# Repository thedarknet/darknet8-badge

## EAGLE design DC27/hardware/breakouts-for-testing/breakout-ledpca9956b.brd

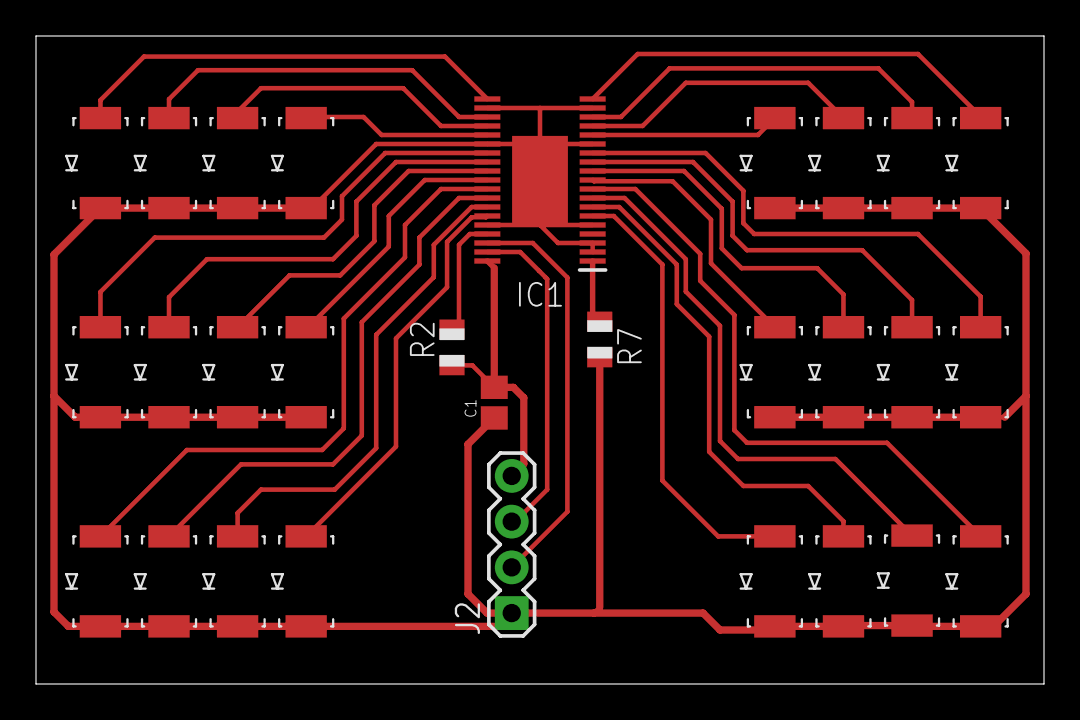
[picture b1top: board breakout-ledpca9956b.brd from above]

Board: 2 copper layers, 56.0 x 36.0 mm, 30 parts (0 on the bottom side), 30 nets.

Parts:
C1: 0.1 uF; C0805
IC1: PCA9956BTWY; SOP50P640X110-39N
J2: 1X04
LED1, LED2, LED3, LED4, LED5, LED6, LED7, LED8, LED9, LED10, LED11, LED12, LED13, LED14, LED15, LED16, LED17, LED18, LED19, LED20, LED21, LED22, LED23, LED24: GULLWING_LED
R2: 10 K; R0805
R7: 2 K; R0805
U$2: CMD_C0DE_LOGO

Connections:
GND: C1.1, IC1.2, IC1.3, IC1.5, IC1.14, IC1.18, IC1.21, IC1.25, IC1.34, IC1.39, J2.1, LED1.C, LED2.C, LED3.C, LED4.C, LED5.C, LED6.C, LED7.C, LED8.C, LED9.C, LED10.C, LED11.C, LED12.C, LED13.C, LED14.C, LED15.C, LED16.C, LED17.C, LED18.C, LED19.C, LED20.C, LED21.C, LED22.C, LED23.C, LED24.C, R7.2
unnamed: IC1.6, LED1.A
unnamed: IC1.7, LED2.A
unnamed: IC1.8, LED3.A
unnamed: IC1.9, LED4.A
unnamed: IC1.10, LED5.A
unnamed: IC1.11, LED6.A
unnamed: IC1.12, LED7.A
unnamed: IC1.13, LED8.A
unnamed: IC1.15, LED9.A
unnamed: IC1.16, LED10.A
unnamed: IC1.17, LED11.A
unnamed: IC1.19, LED12.A
unnamed: IC1.20, LED13.A
unnamed: IC1.22, LED14.A
unnamed: IC1.23, LED15.A
unnamed: IC1.24, LED16.A
unnamed: IC1.26, LED17.A
unnamed: IC1.27, LED18.A
unnamed: IC1.28, LED19.A
unnamed: IC1.29, LED20.A
unnamed: IC1.30, LED21.A
unnamed: IC1.31, LED22.A
unnamed: IC1.32, LED23.A
unnamed: IC1.33, LED24.A
unnamed: IC1.1, R7.1
unnamed: IC1.35, R2.2
SCL: IC1.36, J2.2
SDA: IC1.37, J2.3
VCC: C1.2, IC1.38, J2.4, R2.1

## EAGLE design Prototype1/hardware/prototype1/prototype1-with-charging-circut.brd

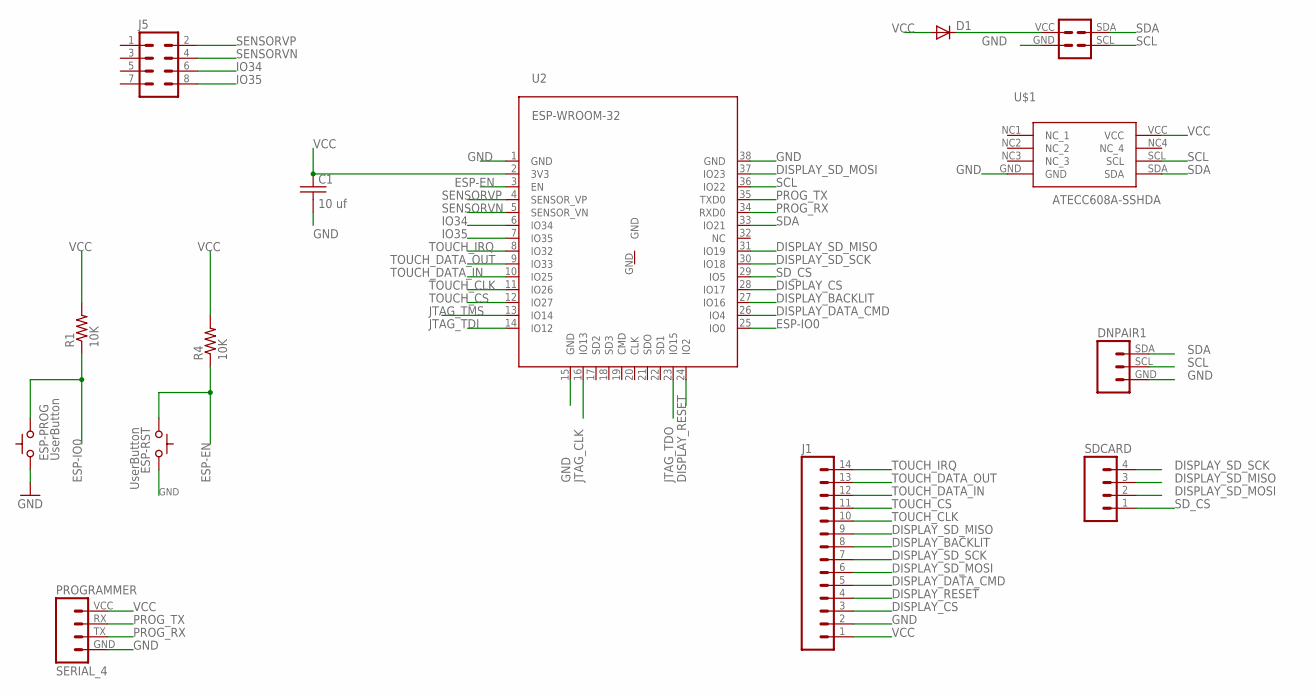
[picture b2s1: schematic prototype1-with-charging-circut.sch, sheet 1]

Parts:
C1: 10 uf; C0805
D1: DIODESMA; SMA-DIODE
DNPAIR1: DARKNET_8_PAIR_CONNECTORPTH; 1X03
ESP-PROG: UserButton; TACTILE-2PIN-NARROW
ESP-RST: UserButton; TACTILE-2PIN-NARROW
J1: M14; 1X14
J5: M04X2; 2X4
PROGRAMMER: SERIAL_4; SERIAL_HEADER_4
R1, R4: 10K; 0805
SDCARD: M04PTH; 1X04
SHITTY_ADDON: SAO1; DC26SHITTY_ADDON_CONNECTOR
U2: ESP-WROOM-32
U$1: ATECC608A-SSHDA; 8-SOIC

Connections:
DISPLAY_BACKLIT: J1.8, U2.27 (IO16)
DISPLAY_CS: J1.3, U2.28 (IO17)
DISPLAY_DATA_CMD: J1.5, U2.26 (IO4)
DISPLAY_RESET: J1.4, U2.24 (IO2)
DISPLAY_SD_MISO: J1.9, SDCARD.3, U2.31 (IO19)
DISPLAY_SD_MOSI: J1.6, SDCARD.2, U2.37 (IO23)
DISPLAY_SD_SCK: J1.7, SDCARD.4, U2.30 (IO18)
ESP-EN: ESP-RST.P$2 (C), R4.1, U2.3 (EN)
ESP-IO0: ESP-PROG.P$1 (A), R1.1, U2.25 (IO0)
GND: C1.2, DNPAIR1.GND, ESP-PROG.P$2 (C), ESP-RST.P$1 (A), J1.2, PROGRAMMER.GND, SHITTY_ADDON.GND, U2.1 (GND), U2.15 (GND), U2.38 (GND), U$1.GND; also elsewhere on the board
IO34: J5.6, U2.6 (IO34)
IO35: J5.8, U2.7 (IO35)
JTAG_CLK: U2.16 (IO13); also elsewhere on the board
JTAG_TDI: U2.14 (IO12); also elsewhere on the board
JTAG_TDO: U2.23 (IO15); also elsewhere on the board
JTAG_TMS: U2.13 (IO14); also elsewhere on the board
unnamed: D1.C, SHITTY_ADDON.VCC
PROG_RX: PROGRAMMER.TX, U2.34 (RXD0); also elsewhere on the board
PROG_TX: PROGRAMMER.RX, U2.35 (TXD0); also elsewhere on the board
SCL: DNPAIR1.SCL, SHITTY_ADDON.SCL, U2.36 (IO22), U$1.SCL
SDA: DNPAIR1.SDA, SHITTY_ADDON.SDA, U2.33 (IO21), U$1.SDA
SD_CS: SDCARD.1, U2.29 (IO5)
SENSORVN: J5.4, U2.5 (SENSOR_VN)
SENSORVP: J5.2, U2.4 (SENSOR_VP)
TOUCH_CLK: J1.10, U2.11 (IO26)
TOUCH_CS: J1.11, U2.12 (IO27)
TOUCH_DATA_IN: J1.12, U2.10 (IO25)
TOUCH_DATA_OUT: J1.13, U2.9 (IO33)
TOUCH_IRQ: J1.14, U2.8 (IO32)
VCC: C1.1, D1.A, J1.1, PROGRAMMER.VCC, R1.2, R4.2, U2.2 (3V3), U$1.VCC; also elsewhere on the board

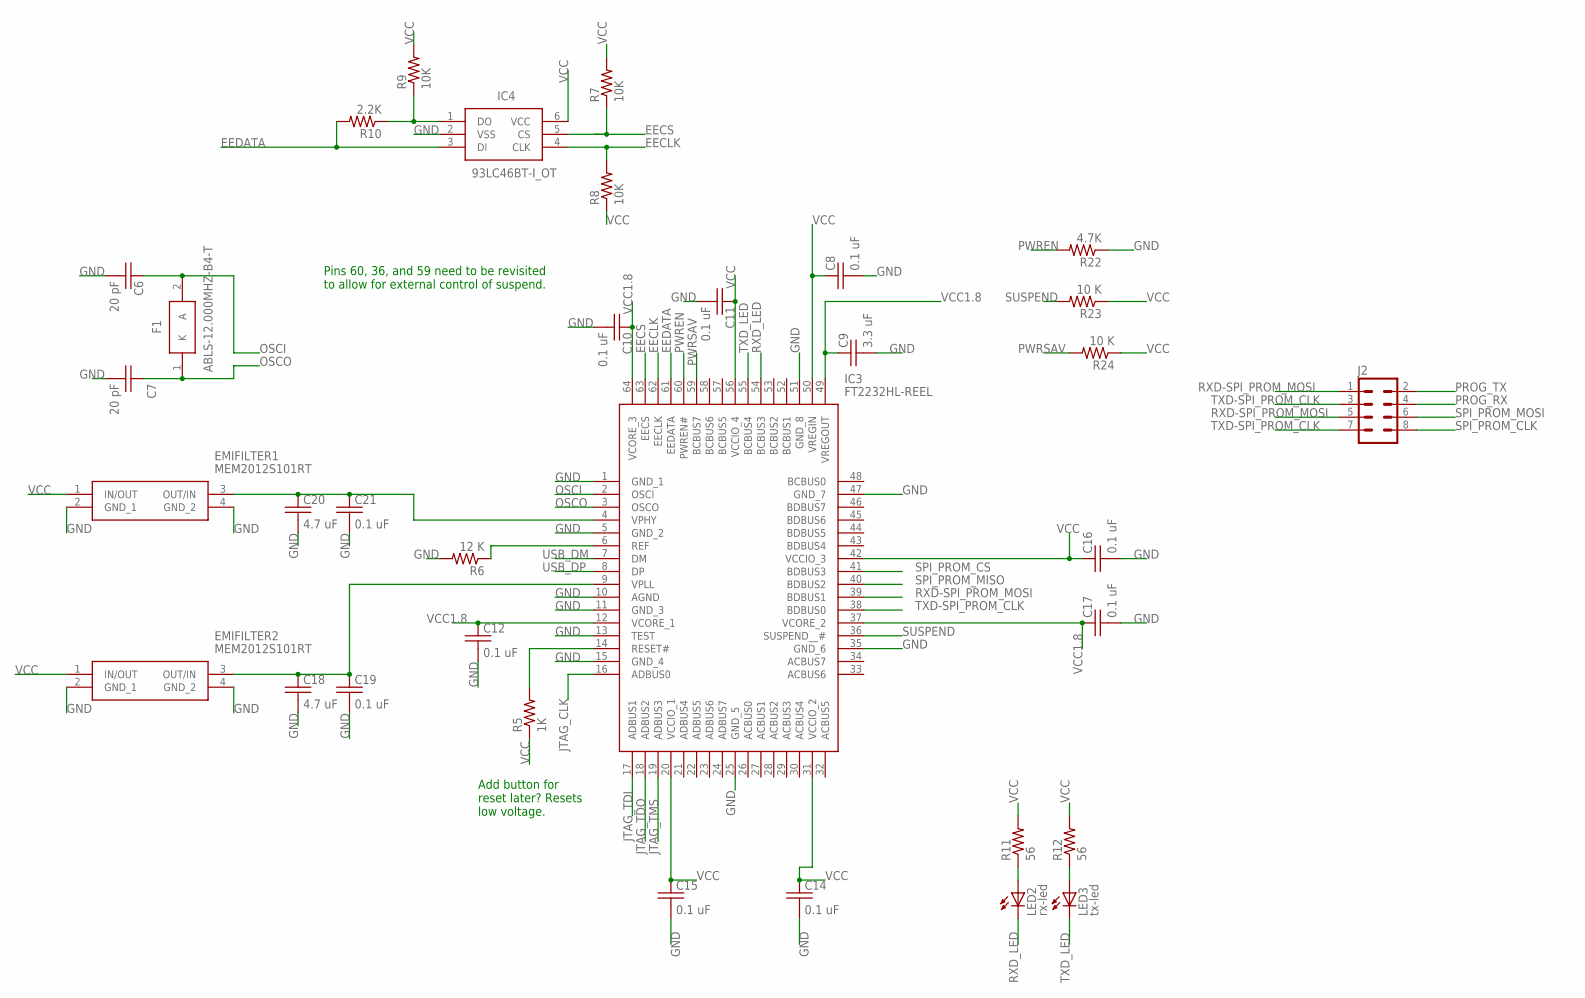
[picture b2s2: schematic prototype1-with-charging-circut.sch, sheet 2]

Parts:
C6, C7: 20 pF; C0805
C8, C10, C11, C12, C14, C15, C16, C17, C19, C21: 0.1 uF; C0805
C9: 3.3 uF; C0805
C18, C20: 4.7 uF; C0805
EMIFILTER1, EMIFILTER2: MEM2012S101RT
F1: ABLS-12.000MHZ-B4-T; HC/49US-(AT49)_1
IC3: FT2232HL-REEL; QFP50P1200X1200X160-64N
IC4: 93LC46BT-I_OT; SOT95P270X145-6N
J2: M04X2; 2X4
LED2: rx-led; LED3MM
LED3: tx-led; LED3MM
R5: 1K; 0805
R6: 12 K; 0805
R7, R8, R9: 10K; 0805
R10: 2.2K; 0805
R11, R12: 56; 0805
R22: 4.7K; 0805
R23, R24: 10 K; 0805

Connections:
EECLK: IC3.62 (EECLK), IC4.4 (CLK), R8.2
EECS: IC3.63 (EECS), IC4.5 (CS), R7.1
EEDATA: IC3.61 (EEDATA), IC4.3 (DI), R10.2
GND: C6.2, C7.2, C8.2, C9.2, C10.2, C11.2, C12.2, C14.2, C15.2, C16.2, C17.2, C18.2, C19.2, C20.2, C21.2, EMIFILTER1.2 (GND_1), EMIFILTER1.4 (GND_2), EMIFILTER2.2 (GND_1), EMIFILTER2.4 (GND_2), IC3.1 (GND_1), IC3.5 (GND_2), IC3.10 (AGND), IC3.11 (GND_3), IC3.13 (TEST), IC3.15 (GND_4), IC3.25 (GND_5), IC3.35 (GND_6), IC3.47 (GND_7), IC3.51 (GND_8), IC4.2 (VSS), R6.2, R22.1; also elsewhere on the board
JTAG_CLK: IC3.16 (ADBUS0); also elsewhere on the board
JTAG_TDI: IC3.17 (ADBUS1); also elsewhere on the board
JTAG_TDO: IC3.18 (ADBUS2); also elsewhere on the board
JTAG_TMS: IC3.19 (ADBUS3); also elsewhere on the board
unnamed: IC3.14 (RESET#), R5.2
unnamed: IC3.6 (REF), R6.1
unnamed: IC4.1 (DO), R9.1, R10.1
unnamed: LED2.A, R11.1
unnamed: LED3.A, R12.1
unnamed: C18.1, C19.1, EMIFILTER2.3 (OUT/IN), IC3.9 (VPLL)
unnamed: C20.1, C21.1, EMIFILTER1.3 (OUT/IN), IC3.4 (VPHY)
OSCI: C6.1, F1.2 (A), IC3.2 (OSCI)
OSCO: C7.1, F1.1 (K), IC3.3 (OSCO)
PROG_RX: J2.4; also elsewhere on the board
PROG_TX: J2.2; also elsewhere on the board
PWREN: IC3.60 (PWREN#), R22.2
PWRSAV: IC3.59 (BCBUS7), R24.2
RXD-SPI_PROM_MOSI: IC3.39 (BDBUS1), J2.1, J2.5
RXD_LED: IC3.54 (BCBUS3), LED2.K (C)
SPI_PROM_CLK: J2.8; also elsewhere on the board
SPI_PROM_CS: IC3.41 (BDBUS3); also elsewhere on the board
SPI_PROM_MISO: IC3.40 (BDBUS2); also elsewhere on the board
SPI_PROM_MOSI: J2.6; also elsewhere on the board
SUSPEND: IC3.36 (SUSPEND__#), R23.2
TXD-SPI_PROM_CLK: IC3.38 (BDBUS0), J2.3, J2.7
TXD_LED: IC3.55 (BCBUS4), LED3.K (C)
USB_DM: IC3.7 (DM); also elsewhere on the board
USB_DP: IC3.8 (DP); also elsewhere on the board
VCC: C8.1, C11.1, C14.1, C15.1, C16.1, EMIFILTER1.1 (IN/OUT), EMIFILTER2.1 (IN/OUT), IC3.20 (VCCIO_1), IC3.31 (VCCIO_2), IC3.42 (VCCIO_3), IC3.50 (VREGIN), IC3.56 (VCCIO_4), IC4.6 (VCC), R5.1, R7.2, R8.1, R9.2, R11.2, R12.2, R23.1, R24.1; also elsewhere on the board
VCC1.8: C9.1, C10.1, C12.1, C17.1, IC3.12 (VCORE_1), IC3.37 (VCORE_2), IC3.49 (VREGOUT), IC3.64 (VCORE_3)

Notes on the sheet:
Add button for reset later? Resets low voltage.
Pins 60, 36, and 59 need to be revisited to allow for external control of suspend.

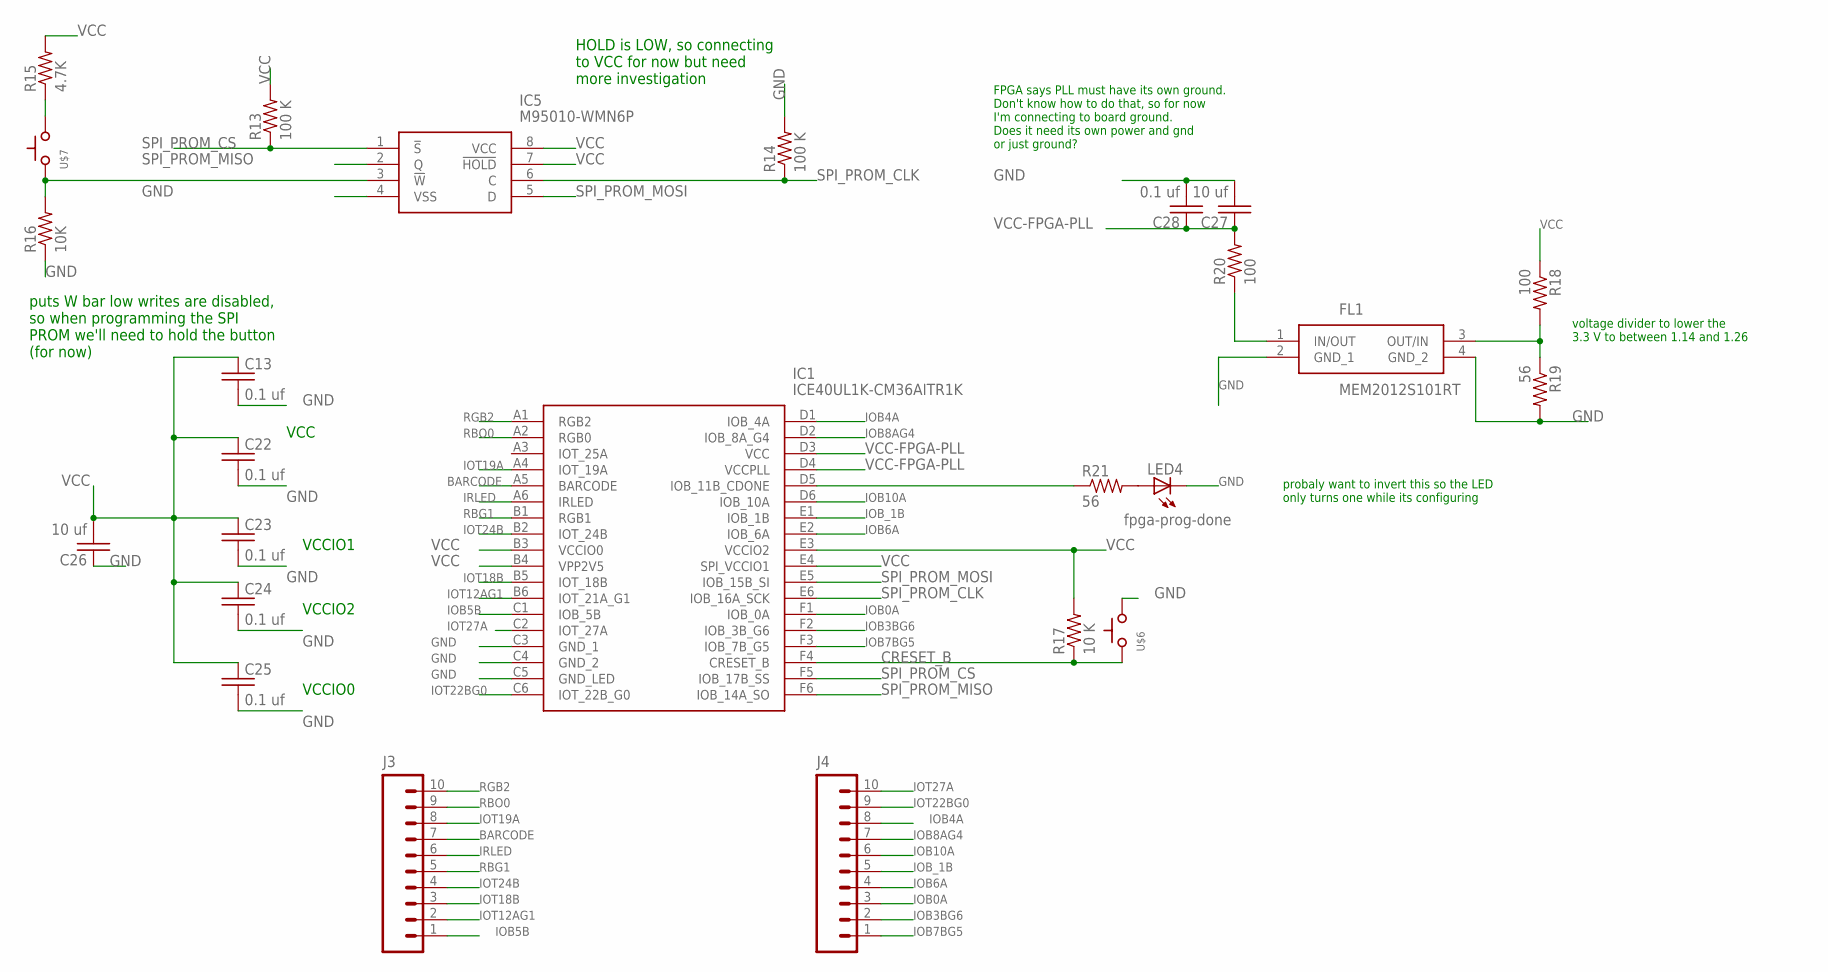
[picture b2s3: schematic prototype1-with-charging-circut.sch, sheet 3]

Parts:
C13, C22, C23, C24, C25, C28: 0.1 uf; C0805
C26, C27: 10 uf; C0805
FL1: MEM2012S101RT
IC1: ICE40UL1K-CM36AITR1K; BGA36C40P6X6_250X250X91
IC5: M95010-WMN6P; SOIC127P600X175-8N
J3, J4: M10SILK_FEMALE_PTH; 1X10
LED4: fpga-prog-done; LED3MM
R13, R14: 100 K; 0805
R15: 4.7K; 0805
R16: 10K; 0805
R17: 10 K; 0805
R18, R20: 100; 0805
R19, R21: 56; 0805
U$6, U$7: SWITCH_TACTILETACTILE-2PIN; TACTILE-2PIN

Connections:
BARCODE: IC1.A5 (BARCODE), J3.7
CRESET_B: IC1.F4 (CRESET_B), R17.1, U$6.P$2 (C)
GND: C13.2, C22.2, C23.2, C24.2, C25.2, C26.1, C27.2, C28.2, FL1.2 (GND_1), FL1.4 (GND_2), IC1.C3 (GND_1), IC1.C4 (GND_2), IC1.C5 (GND_LED), IC5.4 (VSS), LED4.K (C), R14.2, R16.1, R19.2, U$6.P$1 (A); also elsewhere on the board
IOB0A: IC1.F1 (IOB_0A), J4.3
IOB3BG6: IC1.F2 (IOB_3B_G6), J4.2
IOB4A: IC1.D1 (IOB_4A), J4.8
IOB5B: IC1.C1 (IOB_5B), J3.1
IOB6A: IC1.E2 (IOB_6A), J4.4
IOB7BG5: IC1.F3 (IOB_7B_G5), J4.1
IOB8AG4: IC1.D2 (IOB_8A_G4), J4.7
IOB10A: IC1.D6 (IOB_10A), J4.6
IOB_1B: IC1.E1 (IOB_1B), J4.5
IOT12AG1: IC1.B6 (IOT_21A_G1), J3.2
IOT18B: IC1.B5 (IOT_18B), J3.3
IOT19A: IC1.A4 (IOT_19A), J3.8
IOT22BG0: IC1.C6 (IOT_22B_G0), J4.9
IOT24B: IC1.B2 (IOT_24B), J3.4
IOT27A: IC1.C2 (IOT_27A), J4.10
IRLED: IC1.A6 (IRLED), J3.6
unnamed: IC5.3 (!W), R16.2, U$7.P$2 (C)
unnamed: R15.1, U$7.P$1 (A)
unnamed: LED4.A, R21.2
unnamed: FL1.3 (OUT/IN), R18.2, R19.1
unnamed: FL1.1 (IN/OUT), R20.1
unnamed: IC1.D5 (IOB_11B_CDONE), R21.1
RBG1: IC1.B1 (RGB1), J3.5
RBO0: IC1.A2 (RGB0), J3.9
RGB2: IC1.A1 (RGB2), J3.10
SPI_PROM_CLK: IC1.E6 (IOB_16A_SCK), IC5.6 (C), R14.1; also elsewhere on the board
SPI_PROM_CS: IC1.F5 (IOB_17B_SS), IC5.1 (!S), R13.1; also elsewhere on the board
SPI_PROM_MISO: IC1.F6 (IOB_14A_SO), IC5.2 (Q); also elsewhere on the board
SPI_PROM_MOSI: IC1.E5 (IOB_15B_SI), IC5.5 (D); also elsewhere on the board
VCC: C13.1, C22.1, C23.1, C24.1, C25.1, C26.2, IC1.B3 (VCCIO0), IC1.B4 (VPP2V5), IC1.E3 (VCCIO2), IC1.E4 (SPI_VCCIO1), IC5.7 (!HOLD), IC5.8 (VCC), R13.2, R15.2, R17.2, R18.1; also elsewhere on the board
VCC-FPGA-PLL: C27.1, C28.1, IC1.D3 (VCC), IC1.D4 (VCCPLL), R20.2

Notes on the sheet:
HOLD is LOW, so connecting to VCC for now but need more investigation
puts W bar low writes are disabled, so when programming the SPI PROM we'll need to hold the button (for now)
voltage divider to lower the 3.3 V to between 1.14 and 1.26
VCC
VCCIO1
VCCIO2
VCCIO0
FPGA says PLL must have its own ground. Don't know how to do that, so for now I'm connecting to board ground. Does it need its own power and gnd or just ground?
probaly want to invert this so the LED only turns one while its configuring

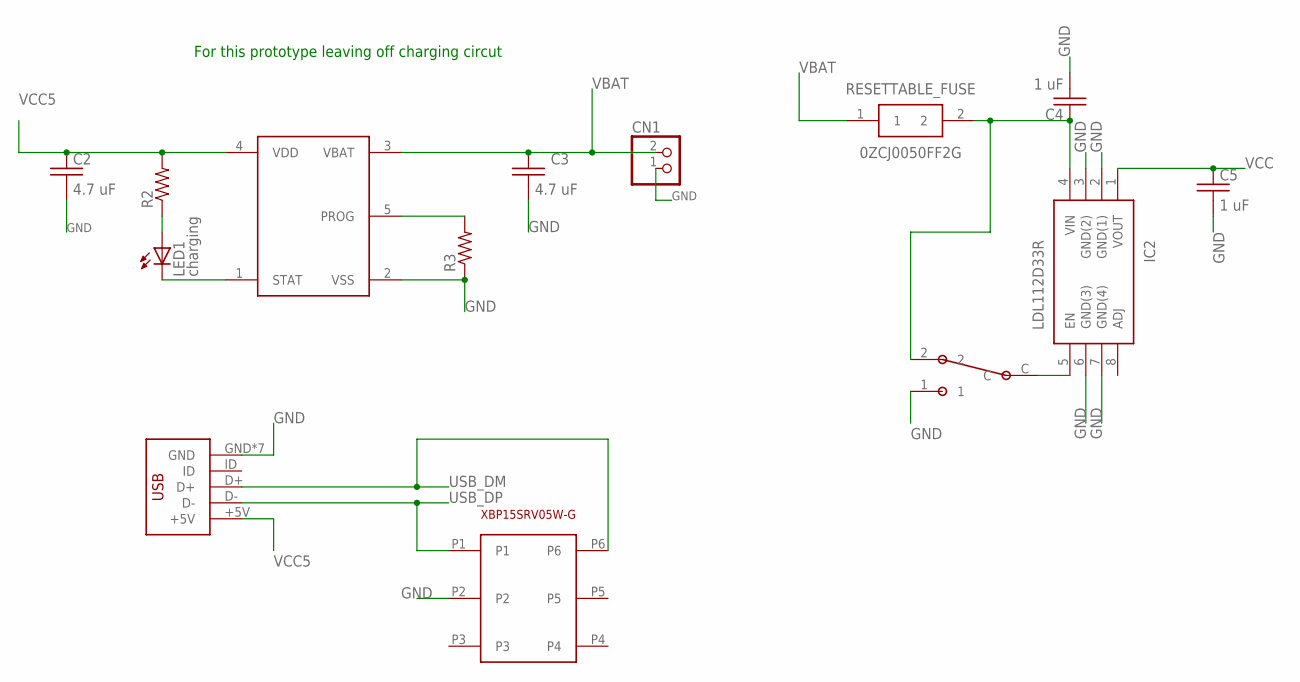
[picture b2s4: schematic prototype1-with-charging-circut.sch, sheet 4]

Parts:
C2, C3: 4.7 uF; C0805
C4, C5: 1 uF; C0805
CN1: JST_2PIN-THM-RA; JST-PH-2-THM-RA
IC2: LDL112D33R; SOIC127P600X175-8N
LED1: charging; LED-0603
R2, R3: RESISTOR0805-RES; 0805
RESETTABLE_FUSE: 0ZCJ0050FF2G; FUSC3216X55N
U$2: DX4R005JJ2DX4R005JJ2; DX4R005JJ2
U$3: XBP15SRV05W-G; SOT-26P-XBP15SRV05W-G
U$4: DS21984E; SOT23-5
U$5: SWITCH_SPDT; SPDT_SSAJ120100

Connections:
GND: C2.2, C3.2, C4.2, C5.2, CN1.1 (2), IC2.2 (GND(1)), IC2.3 (GND(2)), IC2.6 (GND(3)), IC2.7 (GND(4)), R3.1, U$2.GND, U$2.P$6 (GND), U$2.P$7 (GND), U$2.P$8 (GND), U$2.P$9 (GND), U$2.P$10 (GND), U$2.P$11 (GND), U$3.P2, U$4.2 (VSS), U$5.1; also elsewhere on the board
unnamed: LED1.A, R2.1
unnamed: LED1.C, U$4.1 (STAT)
unnamed: R3.2, U$4.5 (PROG)
unnamed: C4.1, IC2.4 (VIN), RESETTABLE_FUSE.2, U$5.2
unnamed: IC2.5 (EN), U$5.C
USB_DM: U$2.D+, U$3.P6; also elsewhere on the board
USB_DP: U$2.D-, U$3.P1; also elsewhere on the board
VBAT: C3.1, CN1.2 (1), RESETTABLE_FUSE.1, U$4.3 (VBAT)
VCC: C5.1, IC2.1 (VOUT); also elsewhere on the board
VCC5: C2.1, R2.2, U$2.+5V, U$4.4 (VDD)

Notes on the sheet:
For this prototype leaving off charging circut

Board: 2 copper layers, 87 parts (0 on the bottom side), 91 nets, no tracks yet.
